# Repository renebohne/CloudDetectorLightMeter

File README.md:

CloudDetectorLightMeter
=======================

An open-source cloud detector and light meter. It detects clouds and reads the light pollution of the sky.

Required Arduino Libraries:
OneWire: http://www.pjrc.com/teensy/td_libs_OneWire.html
FreqMeasure: http://www.pjrc.com/teensy/td_libs_FreqMeasure.html
i2master by Peter Fleury: http://jump.to/fleury or http://homepage.hispeed.ch/peterfleury/avr-software.html

How does a Cloud Detector work?
http://www.kwos.org/clouds_detector.htm

Arduino Pin Mapping:
D8: TSL237
D9: DS18B20 
A4,A5: I2C for MLX90614

SD Card (SPI):
D4,D10,D11,D12,D13

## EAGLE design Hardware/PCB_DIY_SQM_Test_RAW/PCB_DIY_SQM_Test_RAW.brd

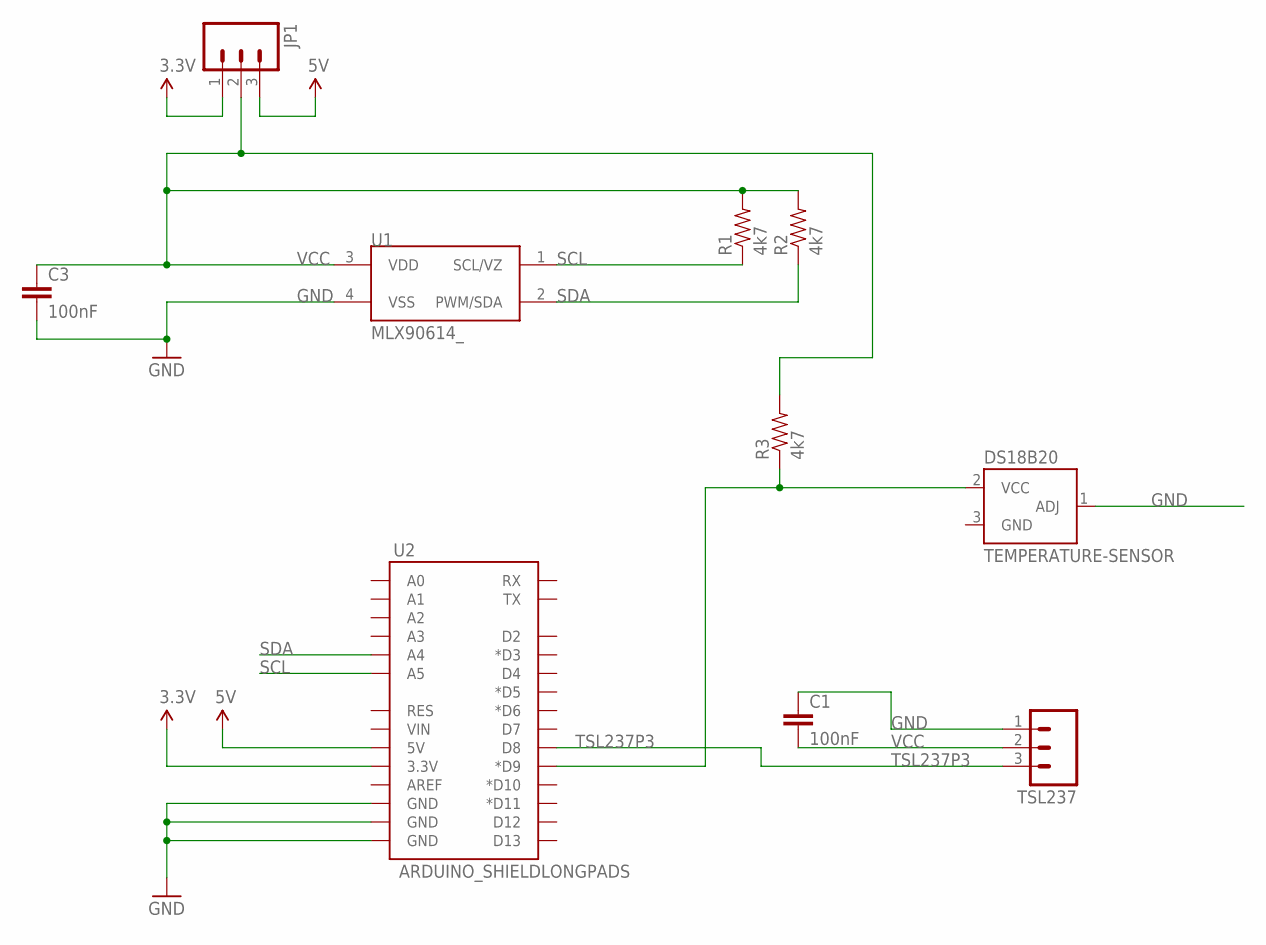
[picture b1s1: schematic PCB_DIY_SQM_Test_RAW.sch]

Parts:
C1, C3: 100nF; CAP-PTH-SMALL
DS18B20: TEMPERATURE-SENSOR; TO-92
JP1: M03LOCK_LONGPADS; 1X03_LOCK_LONGPADS
R1, R2, R3: 4k7; AXIAL-0.4
TSL237: M03LOCK_LONGPADS; 1X03_LOCK_LONGPADS
U1: MLX90614_; TO-39
U2: ARDUINO_SHIELDLONGPADS; DUEMILANOVE_SHIELD_LONGPADS

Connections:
3.3V: JP1.1, U2.3.3V
5V: JP1.3, U2.5V
DS18B20P2: DS18B20.2 (VCC), R3.P$1 (1), U2.D9 (*D9)
GND: C1.1, C3.2, DS18B20.1 (ADJ), TSL237.1, U1.4 (VSS), U2.GND@0 (GND), U2.GND@1 (GND), U2.GND@2 (GND)
SCL: R1.P$1 (1), U1.1 (SCL/VZ), U2.A5
SDA: R2.P$1 (1), U1.2 (PWM/SDA), U2.A4
TSL237P3: TSL237.3, U2.D8
VCC: C1.2, C3.1, JP1.2, R1.P$2 (2), R2.P$2 (2), R3.P$2 (2), TSL237.2, U1.3 (VDD)

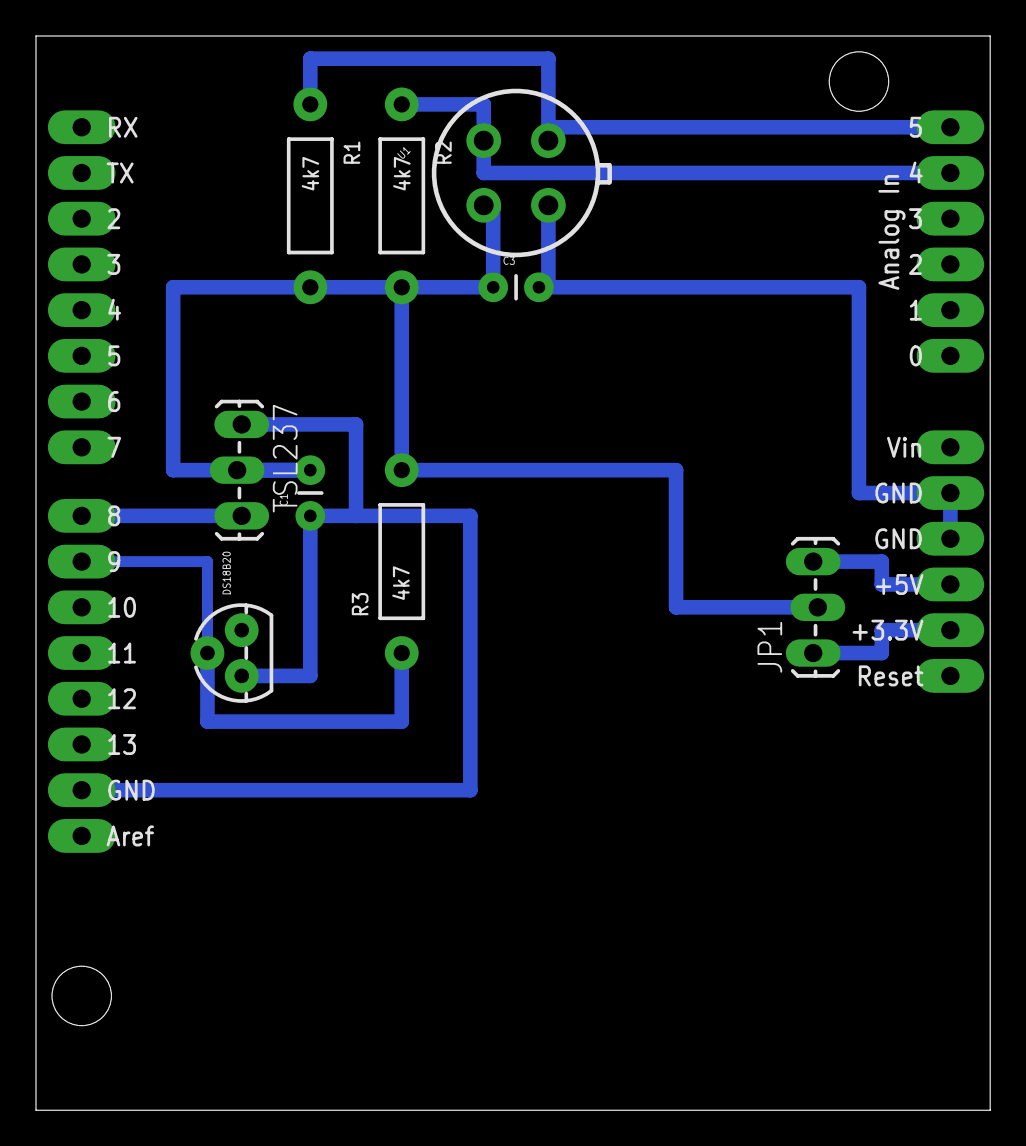
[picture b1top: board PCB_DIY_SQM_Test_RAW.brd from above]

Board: 2 copper layers, 53.0 x 59.7 mm, 10 parts (0 on the bottom side), 8 nets.

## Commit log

2014-01-06 Initial commit: this sketch reads the Arduino Shield and displays the sensor data on the serial console. The Hardware folder contains the layout of the Arduino Shield.
2014-01-06 The DS18B20 now connects to Arduino pin #10 instead of pin #11. This allows us to use the Wireless SD shield (which uses pin #11 for SPI)
2014-01-06 DS18B20 now uses Arduino pin #9 instead of #10, because #10 is used by the SD card of the wireless SD shield. Added support for SD cards. The sketch writes the data to a file called test.txt on the s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
2014-10-14 all resitsors are 4.7 kilo ohms.
2014-10-14 added housing
2016-03-26 Added files via upload
    added an image of the finished Wolki. AISLER can display this image.

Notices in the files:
parts and their libraries:
SparkFun-Sensors: Licensing: CC v3.0 Share-Alike You are welcome to use this library for commercial purposes.
